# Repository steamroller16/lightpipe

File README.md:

lightpipe
=========
Test commit - Sam
Test commit - Adam!

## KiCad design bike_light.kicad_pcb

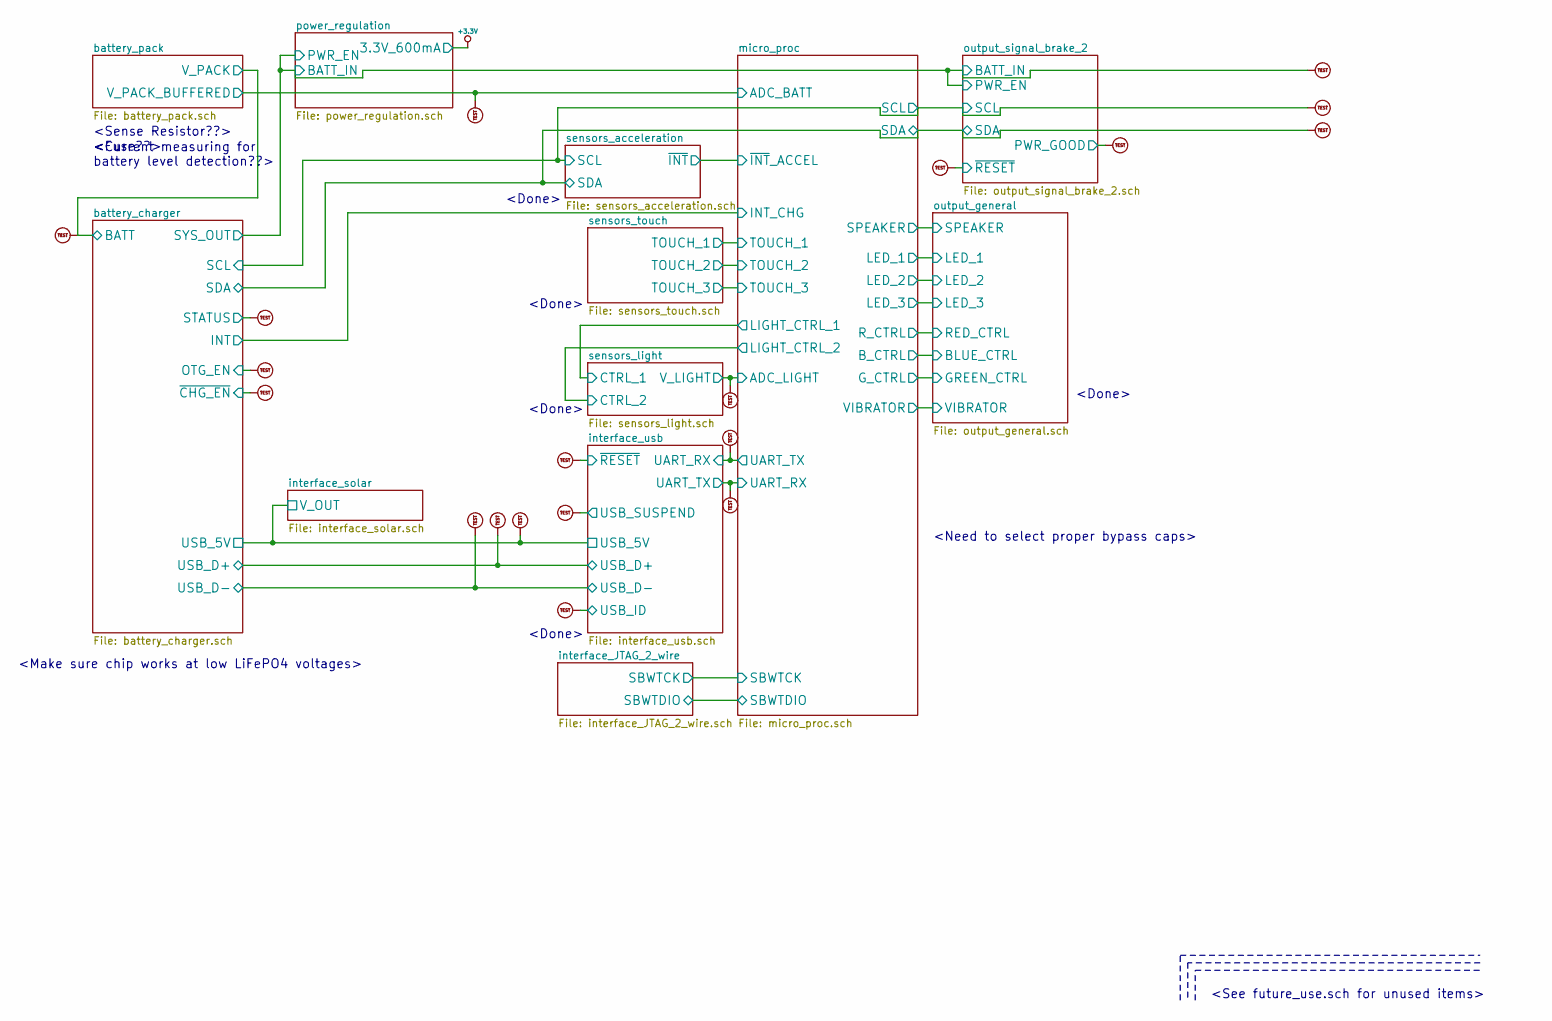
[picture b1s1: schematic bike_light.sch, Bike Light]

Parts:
U1, U2, U3, U4, U5, U6, U7, U8, U9, U10, U11, U12, U13, U14, U15, U16, U17, U18, U19: TEST_PT

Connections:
/battery_charger/BATT: U7.1; also elsewhere on the board
/battery_charger/OTG_EN: U9.1; also elsewhere on the board
/battery_charger/SCL: U2.1; also elsewhere on the board
/battery_charger/SDA: U4.1; also elsewhere on the board
/battery_charger/STATUS: U8.1; also elsewhere on the board
/battery_charger/USB_5V: U18.1; also elsewhere on the board
/battery_charger/USB_D+: U17.1; also elsewhere on the board
/battery_charger/USB_D-: U16.1; also elsewhere on the board
/battery_charger/~CHG_EN: U10.1; also elsewhere on the board
/interface_usb/UART_RX: U12.1; also elsewhere on the board
/interface_usb/USB_ID: U19.1; also elsewhere on the board
/interface_usb/USB_SUSPEND: U15.1; also elsewhere on the board
/interface_usb/~RESET: U13.1; also elsewhere on the board
/micro_proc/ADC_BATT: U3.1; also elsewhere on the board
/micro_proc/ADC_LIGHT: U11.1; also elsewhere on the board
/micro_proc/UART_RX: U14.1; also elsewhere on the board
/output_signal_brake_2/BATT_IN: U1.1; also elsewhere on the board
/output_signal_brake_2/PWR_GOOD: U5.1; also elsewhere on the board
/output_signal_brake_2/~RESET: U6.1; also elsewhere on the board

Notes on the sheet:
<Done>
<Sense Resistor??>
<Fuse??>
<Current measuring for battery level detection??>
<Make sure chip works at low LiFePO4 voltages>
<See future_use.sch for unused items>
<Need to select proper bypass caps>

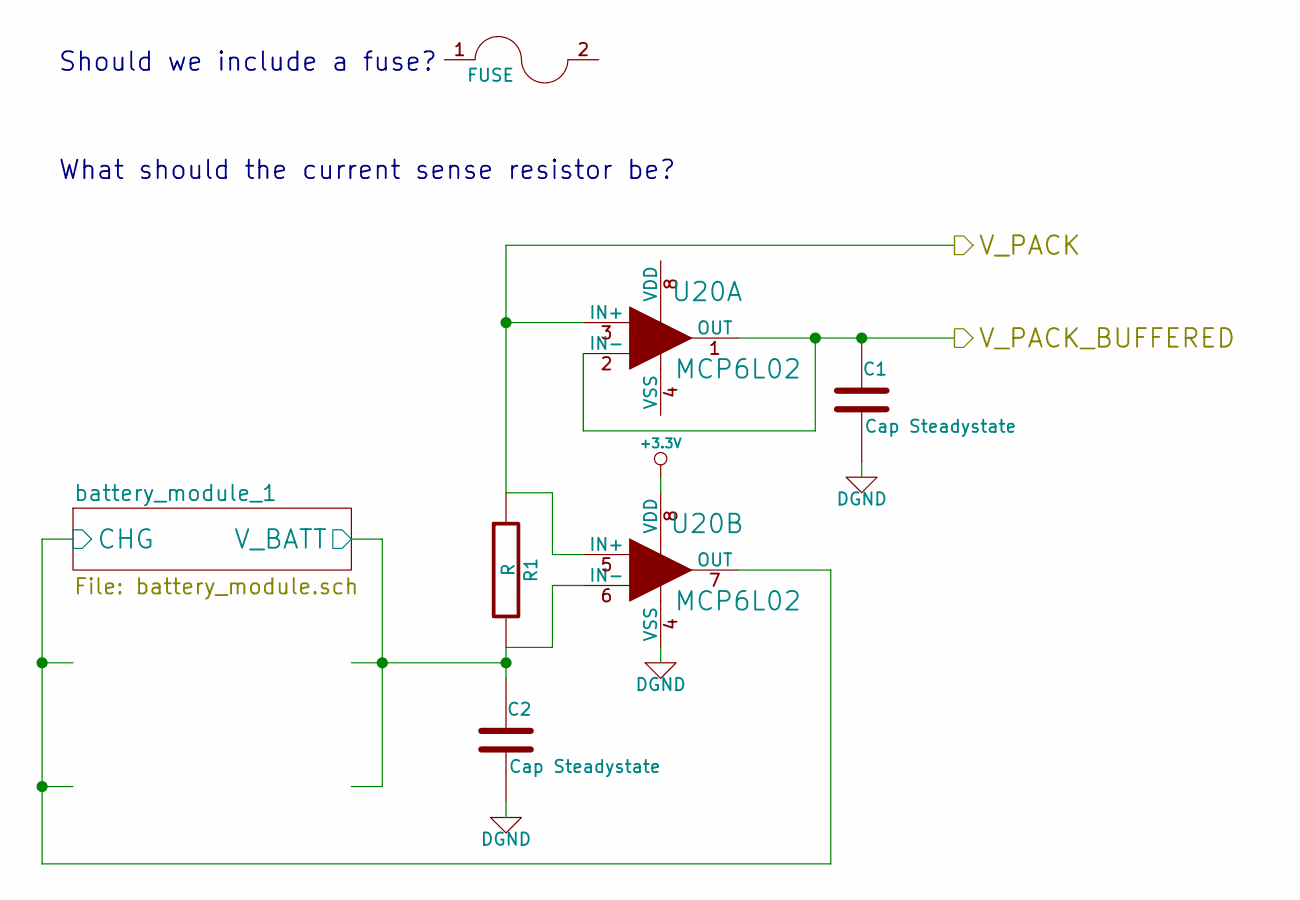
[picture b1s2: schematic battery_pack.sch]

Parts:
C1, C2: Cap Steadystate
R1: R
U20: MCP6L02

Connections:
+3.3V: U20.8 (VDD); also elsewhere on the board
/battery_charger/BATT: R1.1, U20.3 (IN+), U20.5 (IN+); also elsewhere on the board
/battery_pack/battery_module_1/CHG: U20.7 (OUT); also elsewhere on the board
/battery_pack/battery_module_1/V_BATT: C2.1, R1.2, U20.6 (IN-); also elsewhere on the board
/micro_proc/ADC_BATT: C1.1, U20.1 (OUT), U20.2 (IN-); also elsewhere on the board
AGND: C1.2, C2.2, U20.4 (VSS); also elsewhere on the board

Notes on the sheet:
Should we include a fuse?
What should the current sense resistor be?

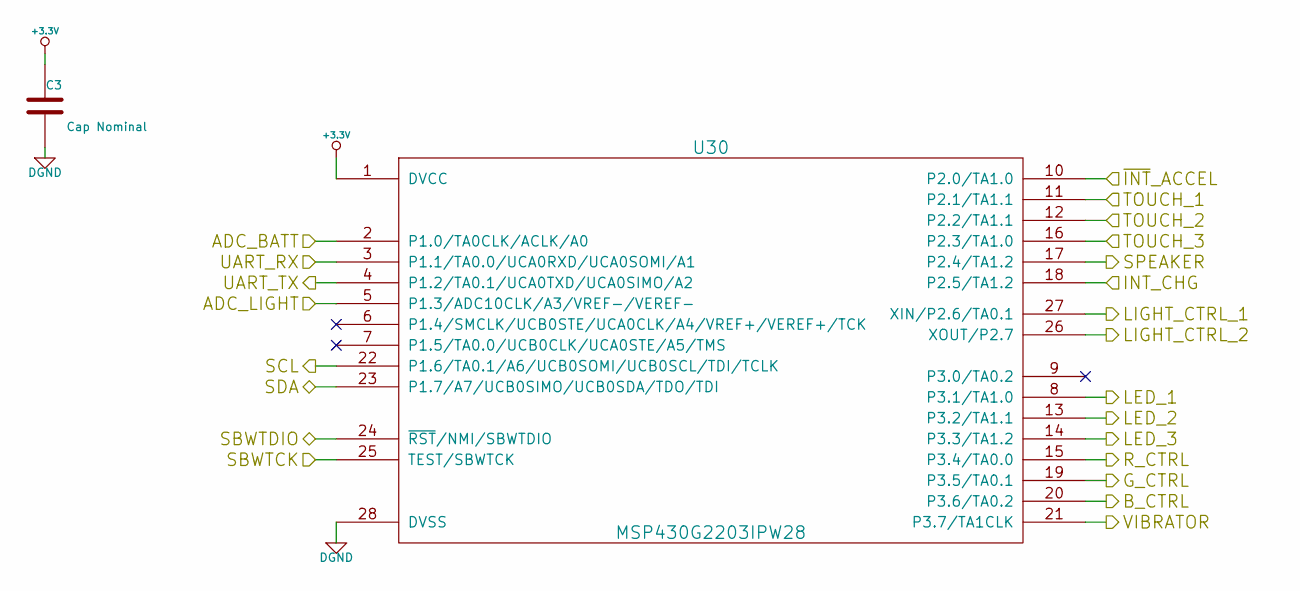
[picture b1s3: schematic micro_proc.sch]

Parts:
C3: Cap Nominal
U30: MSP430G2203IPW28

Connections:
+3.3V: C3.1, U30.1 (DVCC); also elsewhere on the board
/battery_charger/INT: U30.18 (P2.5/TA1.2); also elsewhere on the board
/battery_charger/SCL: U30.22 (P1.6/TA0.1/A6/UCB0SOMI/UCB0SCL/TDI/TCLK); also elsewhere on the board
/battery_charger/SDA: U30.23 (P1.7/A7/UCB0SIMO/UCB0SDA/TDO/TDI); also elsewhere on the board
/interface_JTAG_2_wire/SBWTCK: U30.25 (TEST/SBWTCK); also elsewhere on the board
/interface_JTAG_2_wire/SBWTDIO: U30.24 (~RST~/NMI/SBWTDIO); also elsewhere on the board
/interface_usb/UART_RX: U30.4 (P1.2/TA0.1/UCA0TXD/UCA0SIMO/A2); also elsewhere on the board
/micro_proc/ADC_BATT: U30.2 (P1.0/TA0CLK/ACLK/A0); also elsewhere on the board
/micro_proc/ADC_LIGHT: U30.5 (P1.3/ADC10CLK/A3/VREF-/VEREF-); also elsewhere on the board
/micro_proc/LED_1: U30.8 (P3.1/TA1.0); also elsewhere on the board
/micro_proc/LED_2: U30.13 (P3.2/TA1.1); also elsewhere on the board
/micro_proc/LED_3: U30.14 (P3.3/TA1.2); also elsewhere on the board
/micro_proc/SPEAKER: U30.17 (P2.4/TA1.2); also elsewhere on the board
/micro_proc/TOUCH_1: U30.11 (P2.1/TA1.1); also elsewhere on the board
/micro_proc/TOUCH_2: U30.12 (P2.2/TA1.1); also elsewhere on the board
/micro_proc/TOUCH_3: U30.16 (P2.3/TA1.0); also elsewhere on the board
/micro_proc/UART_RX: U30.3 (P1.1/TA0.0/UCA0RXD/UCA0SOMI/A1); also elsewhere on the board
/micro_proc/VIBRATOR: U30.21 (P3.7/TA1CLK); also elsewhere on the board
/output_general/BLUE_CTRL: U30.20 (P3.6/TA0.2); also elsewhere on the board
/output_general/GREEN_CTRL: U30.19 (P3.5/TA0.1); also elsewhere on the board
/output_general/RED_CTRL: U30.15 (P3.4/TA0.0); also elsewhere on the board
/sensors_acceleration/~INT: U30.10 (P2.0/TA1.0); also elsewhere on the board
/sensors_light/CTRL_1: U30.27 (XIN/P2.6/TA0.1); also elsewhere on the board
/sensors_light/CTRL_2: U30.26 (XOUT/P2.7); also elsewhere on the board
AGND: C3.2, U30.28 (DVSS); also elsewhere on the board

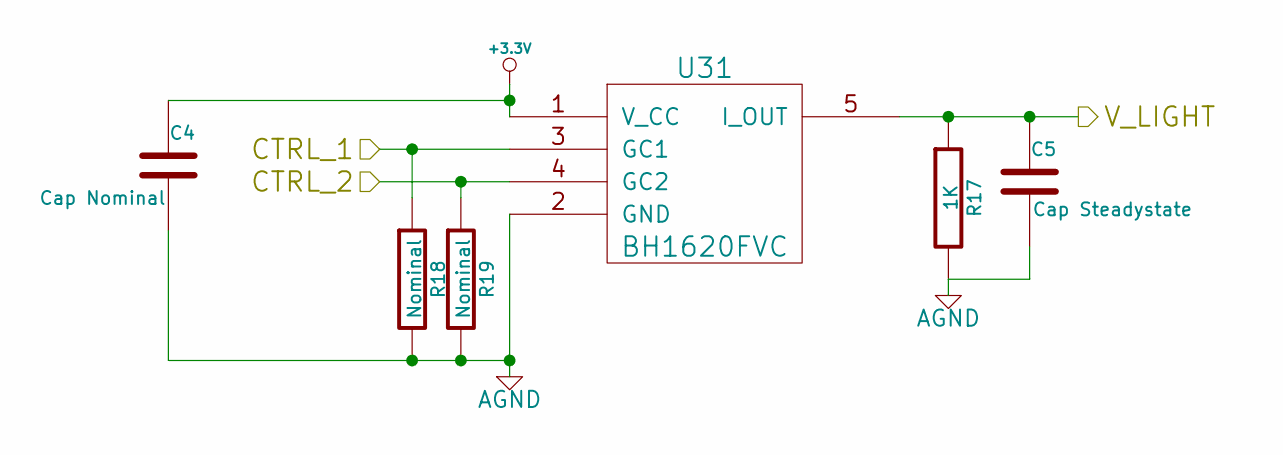
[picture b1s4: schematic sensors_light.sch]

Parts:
C4: Cap Nominal
C5: Cap Steadystate
R17: 1K
R18, R19: Nominal
U31: BH1620FVC

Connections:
+3.3V: C4.1, U31.1 (V_CC); also elsewhere on the board
/micro_proc/ADC_LIGHT: C5.1, R17.1, U31.5 (I_OUT); also elsewhere on the board
/sensors_light/CTRL_1: R18.1, U31.3 (GC1); also elsewhere on the board
/sensors_light/CTRL_2: R19.1, U31.4 (GC2); also elsewhere on the board
AGND: C4.2, C5.2, R17.2, R18.2, R19.2, U31.2 (GND); also elsewhere on the board

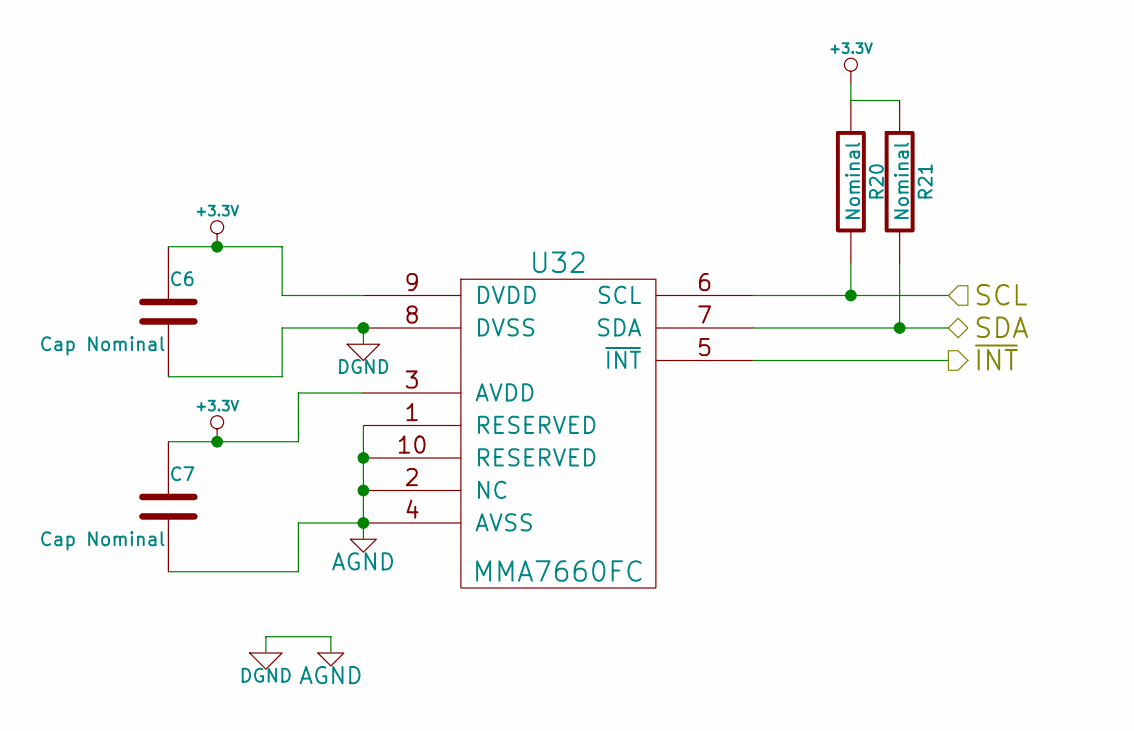
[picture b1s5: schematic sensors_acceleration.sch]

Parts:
C6, C7: Cap Nominal
R20, R21: Nominal
U32: MMA7660FC

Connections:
+3.3V: C6.1, C7.1, R20.1, R21.1, U32.3 (AVDD), U32.9 (DVDD); also elsewhere on the board
/battery_charger/SCL: R20.2, U32.6 (SCL); also elsewhere on the board
/battery_charger/SDA: R21.2, U32.7 (SDA); also elsewhere on the board
/sensors_acceleration/~INT: U32.5 (~INT); also elsewhere on the board
AGND: C6.2, C7.2, U32.1 (RESERVED), U32.2 (NC), U32.4 (AVSS), U32.8 (DVSS), U32.10 (RESERVED); also elsewhere on the board

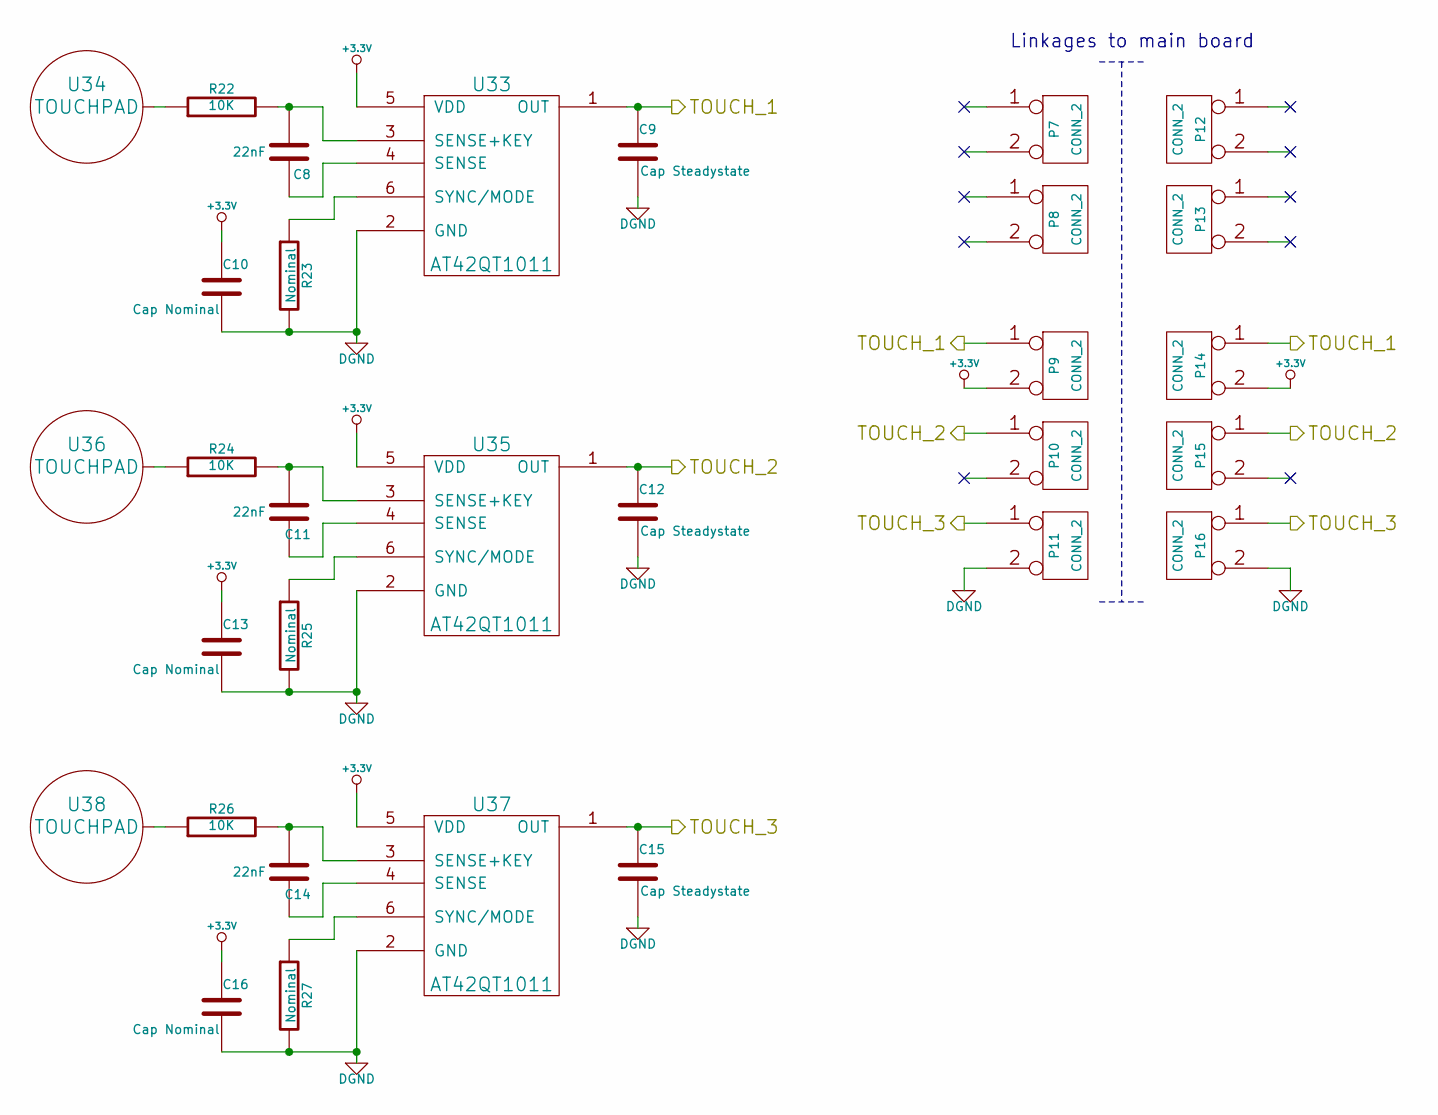
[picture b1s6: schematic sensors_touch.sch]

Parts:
C8, C11, C14: 22nF
C9, C12, C15: Cap Steadystate
C10, C13, C16: Cap Nominal
P7, P8, P9, P10, P11, P12, P13, P14, P15, P16: CONN_2
R22, R24, R26: 10K
R23, R25, R27: Nominal
U33, U35, U37: AT42QT1011
U34, U36, U38: TOUCHPAD

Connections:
+3.3V: C10.1, C13.1, C16.1, P9.2 (PM), P14.2 (PM), U33.5 (VDD), U35.5 (VDD), U37.5 (VDD); also elsewhere on the board
/micro_proc/TOUCH_1: C9.1, P9.1, P14.1, U33.1 (OUT); also elsewhere on the board
/micro_proc/TOUCH_2: C12.1, P10.1, P15.1, U35.1 (OUT); also elsewhere on the board
/micro_proc/TOUCH_3: C15.1, P11.1, P16.1, U37.1 (OUT); also elsewhere on the board
AGND: C9.2, C10.2, C12.2, C13.2, C15.2, C16.2, P11.2 (PM), P16.2 (PM), R23.2, R25.2, R27.2, U33.2 (GND), U35.2 (GND), U37.2 (GND); also elsewhere on the board
unnamed: R25.1, U35.6 (SYNC/MODE)
unnamed: C11.1, U35.4 (SENSE)
unnamed: R24.1, U36.1
unnamed: C11.2, R24.2, U35.3 (SENSE+KEY)
unnamed: R22.1, U34.1
unnamed: C8.2, R22.2, U33.3 (SENSE+KEY)
unnamed: C8.1, U33.4 (SENSE)
unnamed: R23.1, U33.6 (SYNC/MODE)
unnamed: C14.2, R26.2, U37.3 (SENSE+KEY)
unnamed: C14.1, U37.4 (SENSE)
unnamed: R27.1, U37.6 (SYNC/MODE)
unnamed: R26.1, U38.1

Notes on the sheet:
Linkages to main board

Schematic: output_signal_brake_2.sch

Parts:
C17, C18, C19, C20: Cap Nominal
C21, C22: 22uF
C23, C24: 10nF
D36: LED_GENERIC_SMD
L1: 1uH
P1: CONN_6_RA_MALE
P2, P3: CONN_2x2_MALE_RA
P4, P6: CONN_2x2_FEMALE_BACK
P5: CONN_6_FEMALE_FRONT
R37, R38, R39: 270
R40, R43: Nominal
R41: 160k
R42: 300
R44: 75k
U39, U40, U41: TLC59108IPWR
U42: TPS62090

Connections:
+2.5V: C22.1, L1.2, P1.1, P2.1, P2.4, P4.1, P4.4, P5.1, R41.1, R42.1, R43.1, U42.16 (VOS); also elsewhere on the board
+3.3V: C17.1, C18.1, C19.1, C20.1, P1.2, P2.2, P4.2, P5.2, R40.1, U39.2 (A0), U39.20 (VCC), U40.3 (A1), U40.20 (VCC), U41.2 (A0), U41.3 (A1), U41.20 (VCC); also elsewhere on the board
/battery_charger/SCL: P1.3, P3.2, P5.3, P6.2, U39.18 (SCL), U40.18 (SCL), U41.18 (SCL); also elsewhere on the board
/battery_charger/SDA: P1.4, P3.3, P5.4, P6.3, U39.19 (SDA), U40.19 (SDA), U41.19 (SDA); also elsewhere on the board
/output_signal_brake_2/BATT_IN: C21.1, U42.3 (FREQ), U42.10 (AVIN), U42.11 (PVIN), U42.12 (PVIN), U42.13 (EN); also elsewhere on the board
/output_signal_brake_2/PWR_GOOD: R43.2, U42.4 (PG); also elsewhere on the board
/output_signal_brake_2/brake_leds/CATHODE_1: U41.6 (~OUT0); also elsewhere on the board
/output_signal_brake_2/brake_leds/CATHODE_2: U41.7 (~OUT1); also elsewhere on the board
/output_signal_brake_2/brake_leds/CATHODE_3: U41.9 (~OUT2); also elsewhere on the board
/output_signal_brake_2/brake_leds/CATHODE_4: U41.10 (~OUT3); also elsewhere on the board
/output_signal_brake_2/brake_leds/CATHODE_5: U41.11 (~OUT4); also elsewhere on the board
/output_signal_brake_2/brake_leds/CATHODE_6: U41.12 (~OUT5); also elsewhere on the board
/output_signal_brake_2/brake_leds/CATHODE_7: U41.14 (~OUT6); also elsewhere on the board
/output_signal_brake_2/brake_leds/CATHODE_8: U41.15 (~OUT7); also elsewhere on the board
/output_signal_brake_2/signal_leds_back/CATHODE_1: U40.6 (~OUT0); also elsewhere on the board
/output_signal_brake_2/signal_leds_back/CATHODE_2: U40.7 (~OUT1); also elsewhere on the board
/output_signal_brake_2/signal_leds_back/CATHODE_3: U40.9 (~OUT2); also elsewhere on the board
/output_signal_brake_2/signal_leds_back/CATHODE_4: U40.10 (~OUT3); also elsewhere on the board
/output_signal_brake_2/signal_leds_back/CATHODE_5: U40.11 (~OUT4); also elsewhere on the board
/output_signal_brake_2/signal_leds_back/CATHODE_6: U40.12 (~OUT5); also elsewhere on the board
/output_signal_brake_2/signal_leds_back/CATHODE_7: U40.14 (~OUT6); also elsewhere on the board
/output_signal_brake_2/signal_leds_back/CATHODE_8: U40.15 (~OUT7); also elsewhere on the board
/output_signal_brake_2/signal_leds_front/CATHODE_1: U39.6 (~OUT0); also elsewhere on the board
/output_signal_brake_2/signal_leds_front/CATHODE_2: U39.7 (~OUT1); also elsewhere on the board
/output_signal_brake_2/signal_leds_front/CATHODE_3: U39.9 (~OUT2); also elsewhere on the board
/output_signal_brake_2/signal_leds_front/CATHODE_4: U39.10 (~OUT3); also elsewhere on the board
/output_signal_brake_2/signal_leds_front/CATHODE_5: U39.11 (~OUT4); also elsewhere on the board
/output_signal_brake_2/signal_leds_front/CATHODE_6: U39.12 (~OUT5); also elsewhere on the board
/output_signal_brake_2/signal_leds_front/CATHODE_7: U39.14 (~OUT6); also elsewhere on the board
/output_signal_brake_2/signal_leds_front/CATHODE_8: U39.15 (~OUT7); also elsewhere on the board
/output_signal_brake_2/~RESET: P1.5, P2.3, P4.3, P5.5, R40.2, U39.17 (~RESET), U40.17 (~RESET), U41.17 (~RESET); also elsewhere on the board
AGND: C17.2, C18.2, C19.2, C20.2, C21.2, C22.2, C24.2, D36.2 (Cathode), P1.6, P3.1, P3.4, P5.6, P6.1, P6.4, R37.2, R38.2, R39.2, R44.2, U39.3 (A1), U39.4 (A2), U39.5 (A3), U39.8 (GND), U39.13 (GND), U39.16 (GND), U40.2 (A0), U40.4 (A2), U40.5 (A3), U40.8 (GND), U40.13 (GND), U40.16 (GND), U41.4 (A2), U41.5 (A3), U41.8 (GND), U41.13 (GND), U41.16 (GND), U42.6 (AGND), U42.14 (PGND), U42.15 (PGND), U42.17 (Thermal_Pad); also elsewhere on the board
unnamed: D36.1 (Anode), R42.2
unnamed: R38.1, U40.1 (R_EXT)
unnamed: R37.1, U39.1 (R_EXT)
unnamed: R39.1, U41.1 (R_EXT)
unnamed: L1.1, U42.1 (SW), U42.2 (SW)
unnamed: C23.2, U42.8 (CN)
unnamed: C24.1, U42.9 (SS)
unnamed: C23.1, U42.7 (CP)
unnamed: R41.2, R44.1, U42.5 (FB)

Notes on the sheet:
Turn Signal
Brake Signal
70mA
Slave Address 1000-001x
Slave Address 1000-011x
L/R Handlebars
Helmet
Battery to 2.5V Buck Power Supply
Indicator LED
1.9V @ 2mA
Slave Address 1000-010x
1.4MHz operation
-30%< L <+20%
-50% < C < +20%

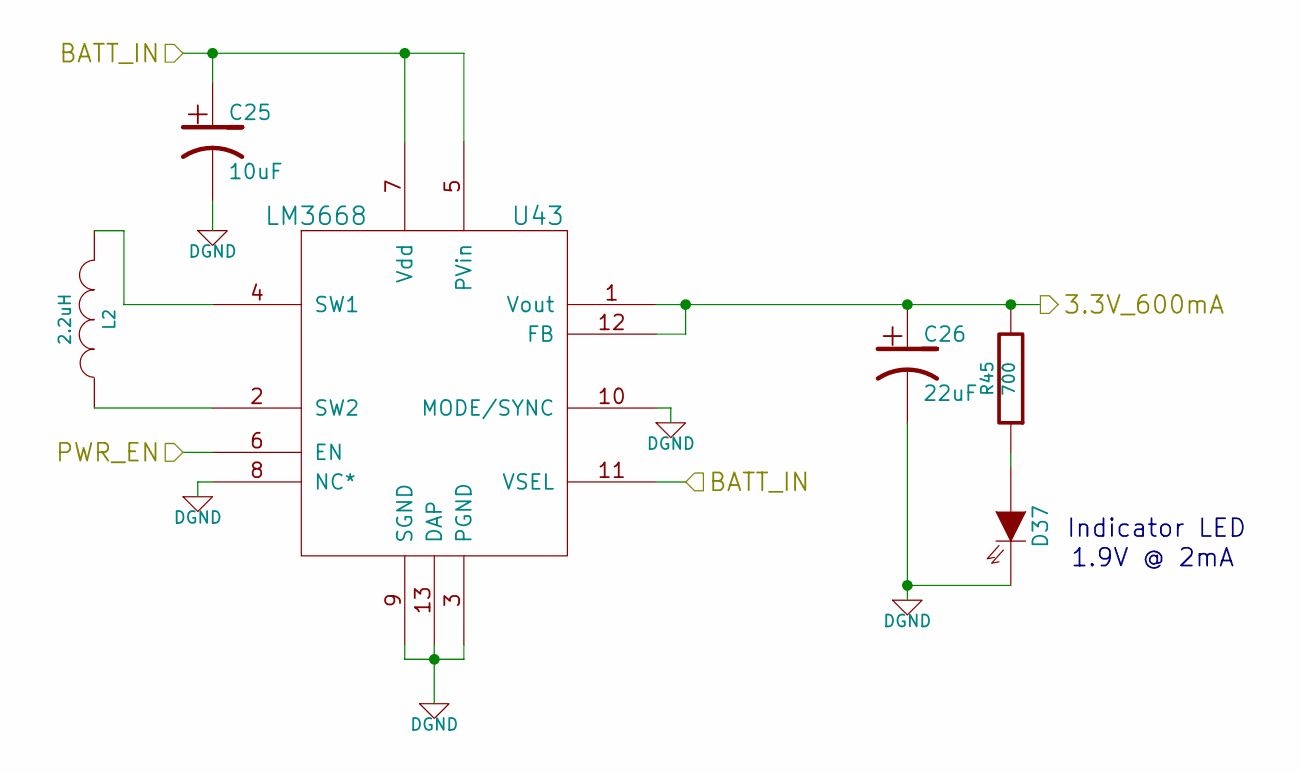
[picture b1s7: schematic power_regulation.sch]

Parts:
C25: 10uF
C26: 22uF
D37: LED_GENERIC_SMD
L2: 2.2uH
R45: 700
U43: LM3668

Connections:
+3.3V: C26.1, R45.2, U43.1 (Vout), U43.12 (FB); also elsewhere on the board
/output_signal_brake_2/BATT_IN: C25.1, U43.5 (PVin), U43.6 (EN), U43.7 (Vdd), U43.11 (VSEL); also elsewhere on the board
AGND: C25.2, C26.2, D37.2 (Cathode), U43.3 (PGND), U43.8 (NC*), U43.9 (SGND), U43.10 (MODE/SYNC), U43.13 (DAP); also elsewhere on the board
unnamed: D37.1 (Anode), R45.1
unnamed: L2.2, U43.4 (SW1)
unnamed: L2.1, U43.2 (SW2)

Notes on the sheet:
Indicator LED
1.9V @ 2mA

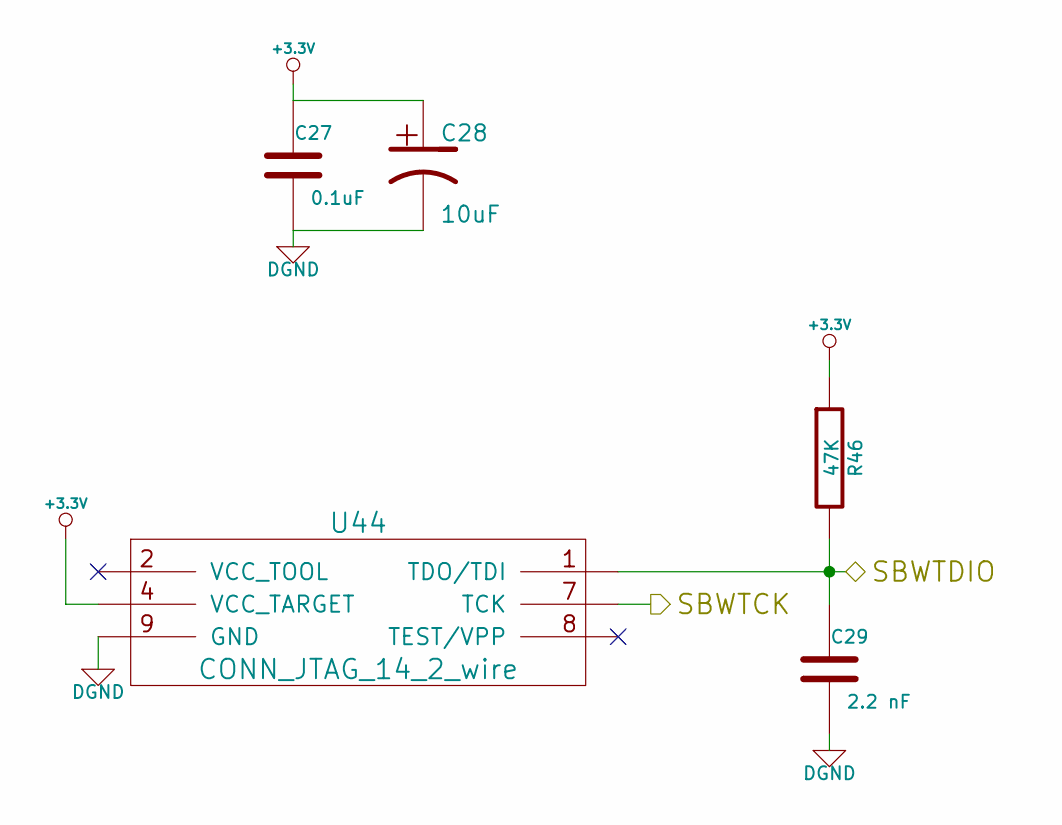
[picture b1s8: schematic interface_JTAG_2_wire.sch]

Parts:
C27: 0.1uF
C28: 10uF
C29: 2.2 nF
R46: 47K
U44: CONN_JTAG_14_2_wire

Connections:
+3.3V: C27.1, C28.1, R46.1, U44.4 (VCC_TARGET); also elsewhere on the board
/interface_JTAG_2_wire/SBWTCK: U44.7 (TCK); also elsewhere on the board
/interface_JTAG_2_wire/SBWTDIO: C29.1, R46.2, U44.1 (TDO/TDI); also elsewhere on the board
AGND: C27.2, C28.2, C29.2, U44.9 (GND); also elsewhere on the board

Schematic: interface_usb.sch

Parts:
C30: Cap Nominal
R47: Nominal
U45: CP2110
U46: ESDR0502N
U47: CONN_USB

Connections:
+3.3V: C30.1, R47.1, U45.5 (V_IO), U45.6 (V_DD), U45.7 (REGIN); also elsewhere on the board
/battery_charger/USB_5V: U45.8 (VBUS), U46.6 (VBUS), U47.1 (+5V); also elsewhere on the board
/battery_charger/USB_D+: U45.3 (D+), U46.2 (NC), U46.5 (D+), U47.3 (D+); also elsewhere on the board
/battery_charger/USB_D-: U45.4 (D-), U46.1 (D-), U47.2 (D-); also elsewhere on the board
/interface_usb/UART_RX: U45.20 (RX); also elsewhere on the board
/interface_usb/USB_ID: U47.4 (ID); also elsewhere on the board
/interface_usb/USB_SUSPEND: U45.11 (SUSPEND); also elsewhere on the board
/interface_usb/~RESET: R47.2, U45.9 (~RST); also elsewhere on the board
/micro_proc/UART_RX: U45.21 (TX); also elsewhere on the board
AGND: C30.2, U45.2 (GND), U46.3 (NC), U46.4 (GND), U47.5 (GND); also elsewhere on the board

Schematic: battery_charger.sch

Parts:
C31: 1uF
C32: 6.8uF
C33: 47nF
C34, C35, C36: 10uF
C37: 4.7uF
D38: LED_GENERIC_SMD
L3: 2.2uH
R48: 700
R49, R50, R51, R52, R56: Nominal
R53, R54: 5.52K
R55: 267
R57, R58: 31.23K
TH1, TH2: NTC 10K
U48: BQ24190

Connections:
+3.3V: R48.1, R49.1, R50.1, R51.1, R52.1; also elsewhere on the board
/battery_charger/BATT: C36.1, U48.13 (BAT), U48.14 (BAT); also elsewhere on the board
/battery_charger/INT: R50.2, U48.7 (INT); also elsewhere on the board
/battery_charger/OTG_EN: R49.2, U48.8 (OTG); also elsewhere on the board
/battery_charger/SCL: R52.2, U48.5 (SCL); also elsewhere on the board
/battery_charger/SDA: R51.2, U48.6 (SDA); also elsewhere on the board
/battery_charger/STATUS: D38.2 (Cathode), U48.4 (STAT); also elsewhere on the board
/battery_charger/USB_5V: C31.1, U48.1 (VBUS), U48.24 (VBUS); also elsewhere on the board
/battery_charger/USB_D+: U48.2 (D+); also elsewhere on the board
/battery_charger/USB_D-: U48.3 (D-); also elsewhere on the board
/battery_charger/~CHG_EN: R56.1, U48.9 (~CE); also elsewhere on the board
/output_signal_brake_2/BATT_IN: C34.1, C35.1, L3.2, U48.15 (SYS), U48.16 (SYS); also elsewhere on the board
AGND: C31.2, C32.2, C34.2, C35.2, C36.2, C37.2, R55.1, R56.2, R57.2, R58.2, TH1.2, TH2.2, U48.17 (PGND), U48.18 (PGND), U48.25 (PowerPAD); also elsewhere on the board
unnamed: C33.1, L3.1, U48.19 (SW), U48.20 (SW)
unnamed: C33.2, U48.21 (BTST)
unnamed: C32.1, U48.23 (PMID)
unnamed: D38.1 (Anode), R48.2
unnamed: R53.2, R57.1, TH1.1, U48.11 (TS1)
unnamed: R54.2, R58.1, TH2.1, U48.12 (TS2)
unnamed: C37.1, R53.1, R54.1, U48.22 (REGN)
unnamed: R55.2, U48.10 (I_LIM)

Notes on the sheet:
X7R or X5R, 25V+ 2A+
X7R or X5R, 6V+ 109mA+
4A @ 3.65V Charging
Charger limited to 2A @ 5V
I_SAT >= 4A + 0.5*I_RIPPLE = 4 + .5*.378 = 4.189A
I_RIPPLE = 5*.5*.5/1.5/2.2 = 0.378A
Indicator LED
1.9V @ 2mA

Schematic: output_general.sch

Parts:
D7, D8, D9: RBG_LED
JP1: JUMPER3
Q2, Q4, Q5, Q6, Q7, Q8, Q9: DMN65D8L; SOT23
R28, R29, R30: 120
SP1: BUZZER PIEZO 25VP-P SMD
SP2: VIBRATIONAL MOTOR (COIN)

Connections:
+2.5V: JP1.1; also elsewhere on the board
+3.3V: JP1.3, Q4.3 (D), Q5.3 (D), Q6.3 (D); also elsewhere on the board
/micro_proc/LED_1: Q4.1 (G); also elsewhere on the board
/micro_proc/LED_2: Q5.1 (G); also elsewhere on the board
/micro_proc/LED_3: Q6.1 (G); also elsewhere on the board
/micro_proc/SPEAKER: SP1.1; also elsewhere on the board
/micro_proc/VIBRATOR: Q2.1 (G); also elsewhere on the board
/output_general/BLUE_CTRL: Q7.1 (G); also elsewhere on the board
/output_general/GREEN_CTRL: Q8.1 (G); also elsewhere on the board
/output_general/RED_CTRL: Q9.1 (G); also elsewhere on the board
AGND: Q2.2 (S), Q7.2 (S), Q8.2 (S), Q9.2 (S), SP1.2; also elsewhere on the board
unnamed: D9.4 (ANODE+), Q6.2 (S)
unnamed: D8.4 (ANODE+), Q5.2 (S)
unnamed: D7.4 (ANODE+), Q4.2 (S)
unnamed: D7.1 (BLUE), D8.1 (BLUE), D9.1 (BLUE), Q7.3 (D)
unnamed: JP1.2, SP2.1
unnamed: Q2.3 (D), SP2.2
unnamed: D7.3 (GREEN), D8.3 (GREEN), D9.3 (GREEN), Q8.3 (D)
unnamed: D8.2 (RED), R29.1
unnamed: D7.2 (RED), R28.1
unnamed: Q9.3 (D), R28.2, R29.2, R30.2
unnamed: D9.2 (RED), R30.1

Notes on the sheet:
120mA Max
2.7V -3.3V DC

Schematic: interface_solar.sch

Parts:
D32: LED_GENERIC_SMD
D33: DIODESCH
P17: SOLAR_CONN
R13: 1.55K

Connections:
/battery_charger/USB_5V: D33.2 (K); also elsewhere on the board
/interface_solar/SOLAR(+): D33.1 (A), P17.1, R13.1
AGND: D32.2 (Cathode), P17.2 (PM); also elsewhere on the board
unnamed: D32.1 (Anode), R13.2

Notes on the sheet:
2mA @ 1.9 V
+5.67V Max 50mA Max

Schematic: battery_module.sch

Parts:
BT1: BATTERY
D1, D2: MBR1045ULPS
Q1: AON7611
R2: 1.58M
R3, R4: Nominal
R5: 102K
R6: 191K
U21: 74LVC2G06
U22: TPS3700
U23: NC7WZ08

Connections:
+3.3V: R3.1, R4.1, U21.5 (VCC), U22.5 (VDD), U23.8 (VCC); also elsewhere on the board
/battery_pack/battery_module_1/CHG: U21.1 (A), U23.1 (A); also elsewhere on the board
/battery_pack/battery_module_1/NMOS_CTRL: Q1.4 (G), U23.7 (Y)
/battery_pack/battery_module_1/PMOS_CTRL: Q1.2 (G), U21.4 (Y)
/battery_pack/battery_module_1/V_BATT: Q1.5 (D); also elsewhere on the board
/battery_pack/battery_module_1/~CHG: U21.6 (Y), U23.5 (A)
/battery_pack/battery_module_1/~OV: R4.2, U22.6 (OUTB), U23.2 (B)
/battery_pack/battery_module_1/~UV: R3.2, U22.1 (OUTA), U23.6 (B)
AGND: BT1.2 (-), R6.2, U21.2 (GND), U22.2 (GND), U23.4 (GND); also elsewhere on the board
unnamed: U21.3 (A), U23.3 (Y)
unnamed: D1.3 (Cathode), Q1.1 (S)
unnamed: BT1.1 (+), D1.1 (Anode), D1.2 (Anode), D2.3 (Cathode), R2.1
unnamed: D2.1 (Anode), D2.2 (Anode), Q1.3 (S)
unnamed: R5.2, R6.1, U22.4 (INB-)
unnamed: R2.2, R5.1, U22.3 (INA+)

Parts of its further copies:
BT2, BT3: BATTERY
Q3: AON7611
R14: Nominal
R15: 102K
R16: 191K
U24, U27: 74LVC2G06
U25, U28: TPS3700
U26, U29: NC7WZ08

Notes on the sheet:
LiFePO4 2.5V <-> 3.65V

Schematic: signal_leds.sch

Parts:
D3, D4, D5, D11, D12, D13, D14: LY-E63F
D6, D10: LY-A67F
R7: 200

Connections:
+2.5V: D3.1 (Anode), D3.2 (Anode), D3.3 (Anode), D4.1 (Anode), D4.2 (Anode), D4.3 (Anode), D5.1 (Anode), D5.2 (Anode), D5.3 (Anode), D6.1 (Anode), D10.1 (Anode), D11.1 (Anode), D11.2 (Anode), D11.3 (Anode), D12.1 (Anode), D12.2 (Anode), D12.3 (Anode), D13.1 (Anode), D13.2 (Anode), D13.3 (Anode), D14.1 (Anode), D14.2 (Anode), D14.3 (Anode), R7.1; also elsewhere on the board
/output_signal_brake_2/signal_leds_front/CATHODE_1: D11.4 (Cathode); also elsewhere on the board
/output_signal_brake_2/signal_leds_front/CATHODE_2: D3.4 (Cathode); also elsewhere on the board
/output_signal_brake_2/signal_leds_front/CATHODE_3: D12.4 (Cathode); also elsewhere on the board
/output_signal_brake_2/signal_leds_front/CATHODE_4: D4.4 (Cathode); also elsewhere on the board
/output_signal_brake_2/signal_leds_front/CATHODE_5: D13.4 (Cathode); also elsewhere on the board
/output_signal_brake_2/signal_leds_front/CATHODE_6: D5.4 (Cathode); also elsewhere on the board
/output_signal_brake_2/signal_leds_front/CATHODE_7: D14.4 (Cathode); also elsewhere on the board
/output_signal_brake_2/signal_leds_front/CATHODE_8: D6.2 (Cathode), D10.2 (Cathode), R7.2; also elsewhere on the board

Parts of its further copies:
D23, D24, D25, D28, D29, D30, D31: LY-E63F
D26, D27: LY-A67F
R12: 200

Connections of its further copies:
+2.5V: D23.1 (Anode), D23.2 (Anode), D23.3 (Anode), D24.1 (Anode), D24.2 (Anode), D24.3 (Anode), D25.1 (Anode), D25.2 (Anode), D25.3 (Anode), D26.1 (Anode), D27.1 (Anode), D28.1 (Anode), D28.2 (Anode), D28.3 (Anode), D29.1 (Anode), D29.2 (Anode), D29.3 (Anode), D30.1 (Anode), D30.2 (Anode), D30.3 (Anode), D31.1 (Anode), D31.2 (Anode), D31.3 (Anode), R12.1; also elsewhere on the board
/output_signal_brake_2/signal_leds_back/CATHODE_1: D28.4 (Cathode); also elsewhere on the board
/output_signal_brake_2/signal_leds_back/CATHODE_2: D23.4 (Cathode); also elsewhere on the board
/output_signal_brake_2/signal_leds_back/CATHODE_3: D29.4 (Cathode); also elsewhere on the board
/output_signal_brake_2/signal_leds_back/CATHODE_4: D24.4 (Cathode); also elsewhere on the board
/output_signal_brake_2/signal_leds_back/CATHODE_5: D30.4 (Cathode); also elsewhere on the board
/output_signal_brake_2/signal_leds_back/CATHODE_6: D25.4 (Cathode); also elsewhere on the board
/output_signal_brake_2/signal_leds_back/CATHODE_7: D31.4 (Cathode); also elsewhere on the board
/output_signal_brake_2/signal_leds_back/CATHODE_8: D26.2 (Cathode), D27.2 (Cathode), R12.2; also elsewhere on the board

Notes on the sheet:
Turn Signal Arrow
Side Turn Signal

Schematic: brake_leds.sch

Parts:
D15, D16, D17, D18, D19, D20: LS-E63F
D21, D22: LR-A67F
R8, R9, R10, R11: 200

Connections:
+2.5V: D15.1 (Anode), D15.2 (Anode), D15.3 (Anode), D16.1 (Anode), D16.2 (Anode), D16.3 (Anode), D17.1 (Anode), D17.2 (Anode), D17.3 (Anode), D18.1 (Anode), D18.2 (Anode), D18.3 (Anode), D19.1 (Anode), D19.2 (Anode), D19.3 (Anode), D20.1 (Anode), D20.2 (Anode), D20.3 (Anode), D21.1 (Anode), D22.1 (Anode), R8.1, R9.1, R10.1, R11.1; also elsewhere on the board
/output_signal_brake_2/brake_leds/CATHODE_1: D18.4 (Cathode); also elsewhere on the board
/output_signal_brake_2/brake_leds/CATHODE_2: D15.4 (Cathode); also elsewhere on the board
/output_signal_brake_2/brake_leds/CATHODE_3: D19.4 (Cathode); also elsewhere on the board
/output_signal_brake_2/brake_leds/CATHODE_4: D16.4 (Cathode); also elsewhere on the board
/output_signal_brake_2/brake_leds/CATHODE_5: D20.4 (Cathode); also elsewhere on the board
/output_signal_brake_2/brake_leds/CATHODE_6: D17.4 (Cathode); also elsewhere on the board
/output_signal_brake_2/brake_leds/CATHODE_7: D21.2 (Cathode), R8.2, R9.2; also elsewhere on the board
/output_signal_brake_2/brake_leds/CATHODE_8: D22.2 (Cathode), R10.2, R11.2; also elsewhere on the board

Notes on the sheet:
Brake (Back)
Brake (Side)
